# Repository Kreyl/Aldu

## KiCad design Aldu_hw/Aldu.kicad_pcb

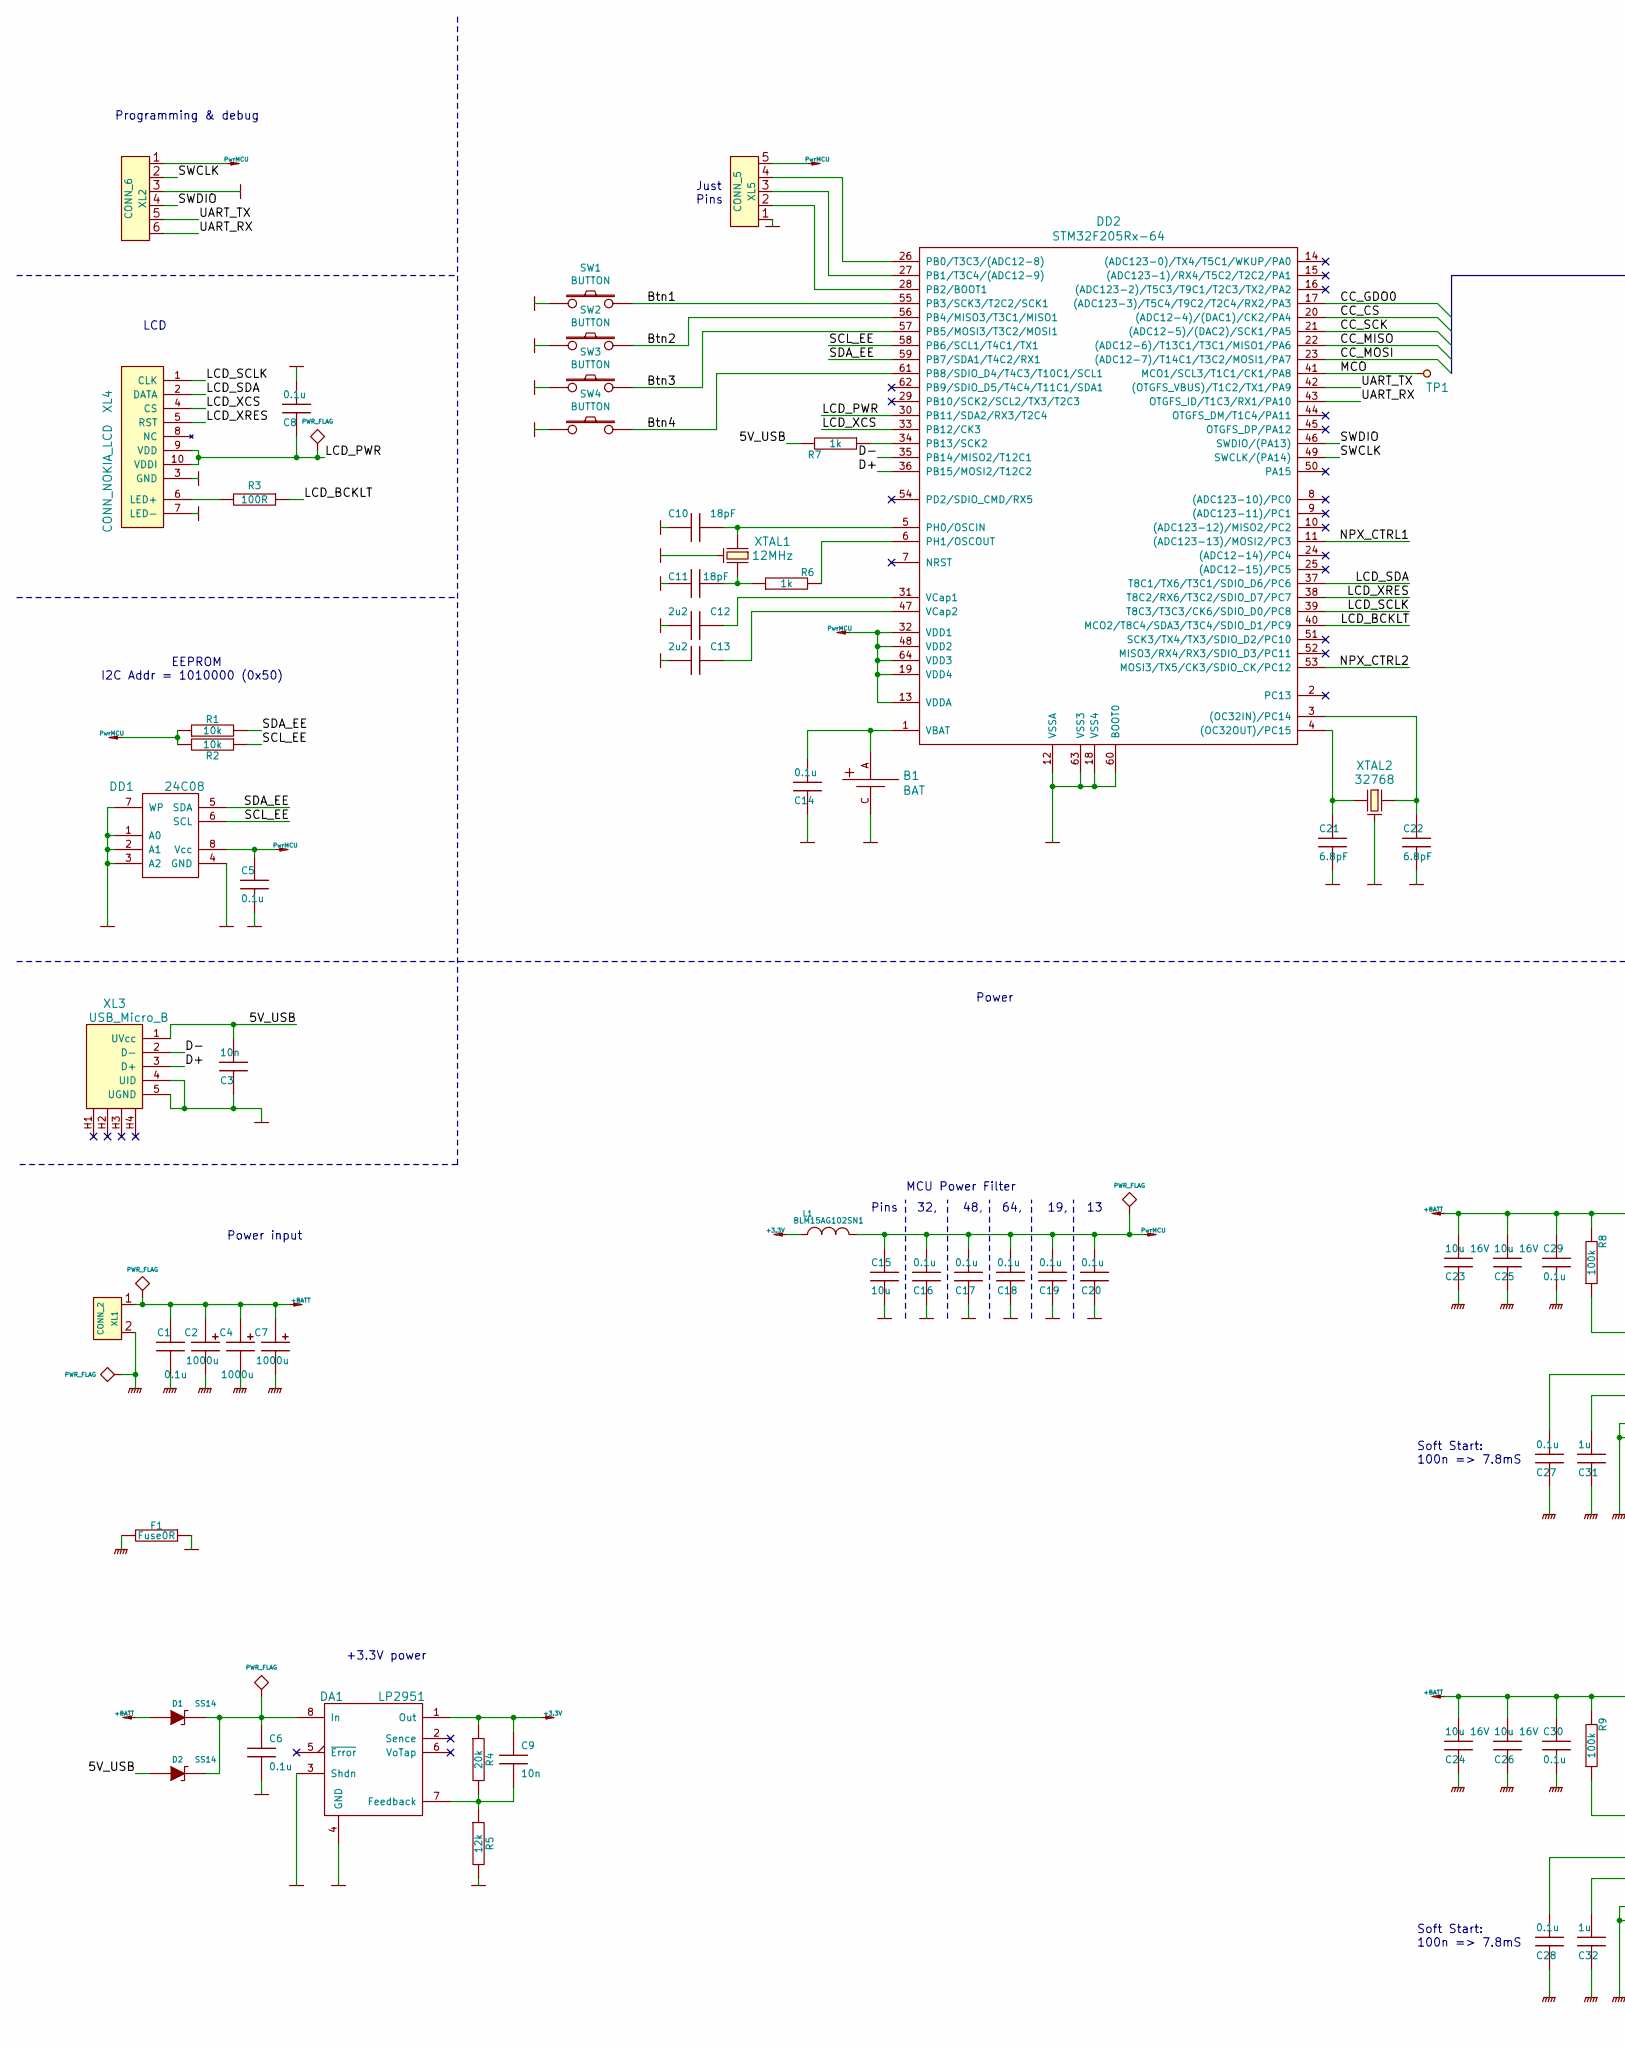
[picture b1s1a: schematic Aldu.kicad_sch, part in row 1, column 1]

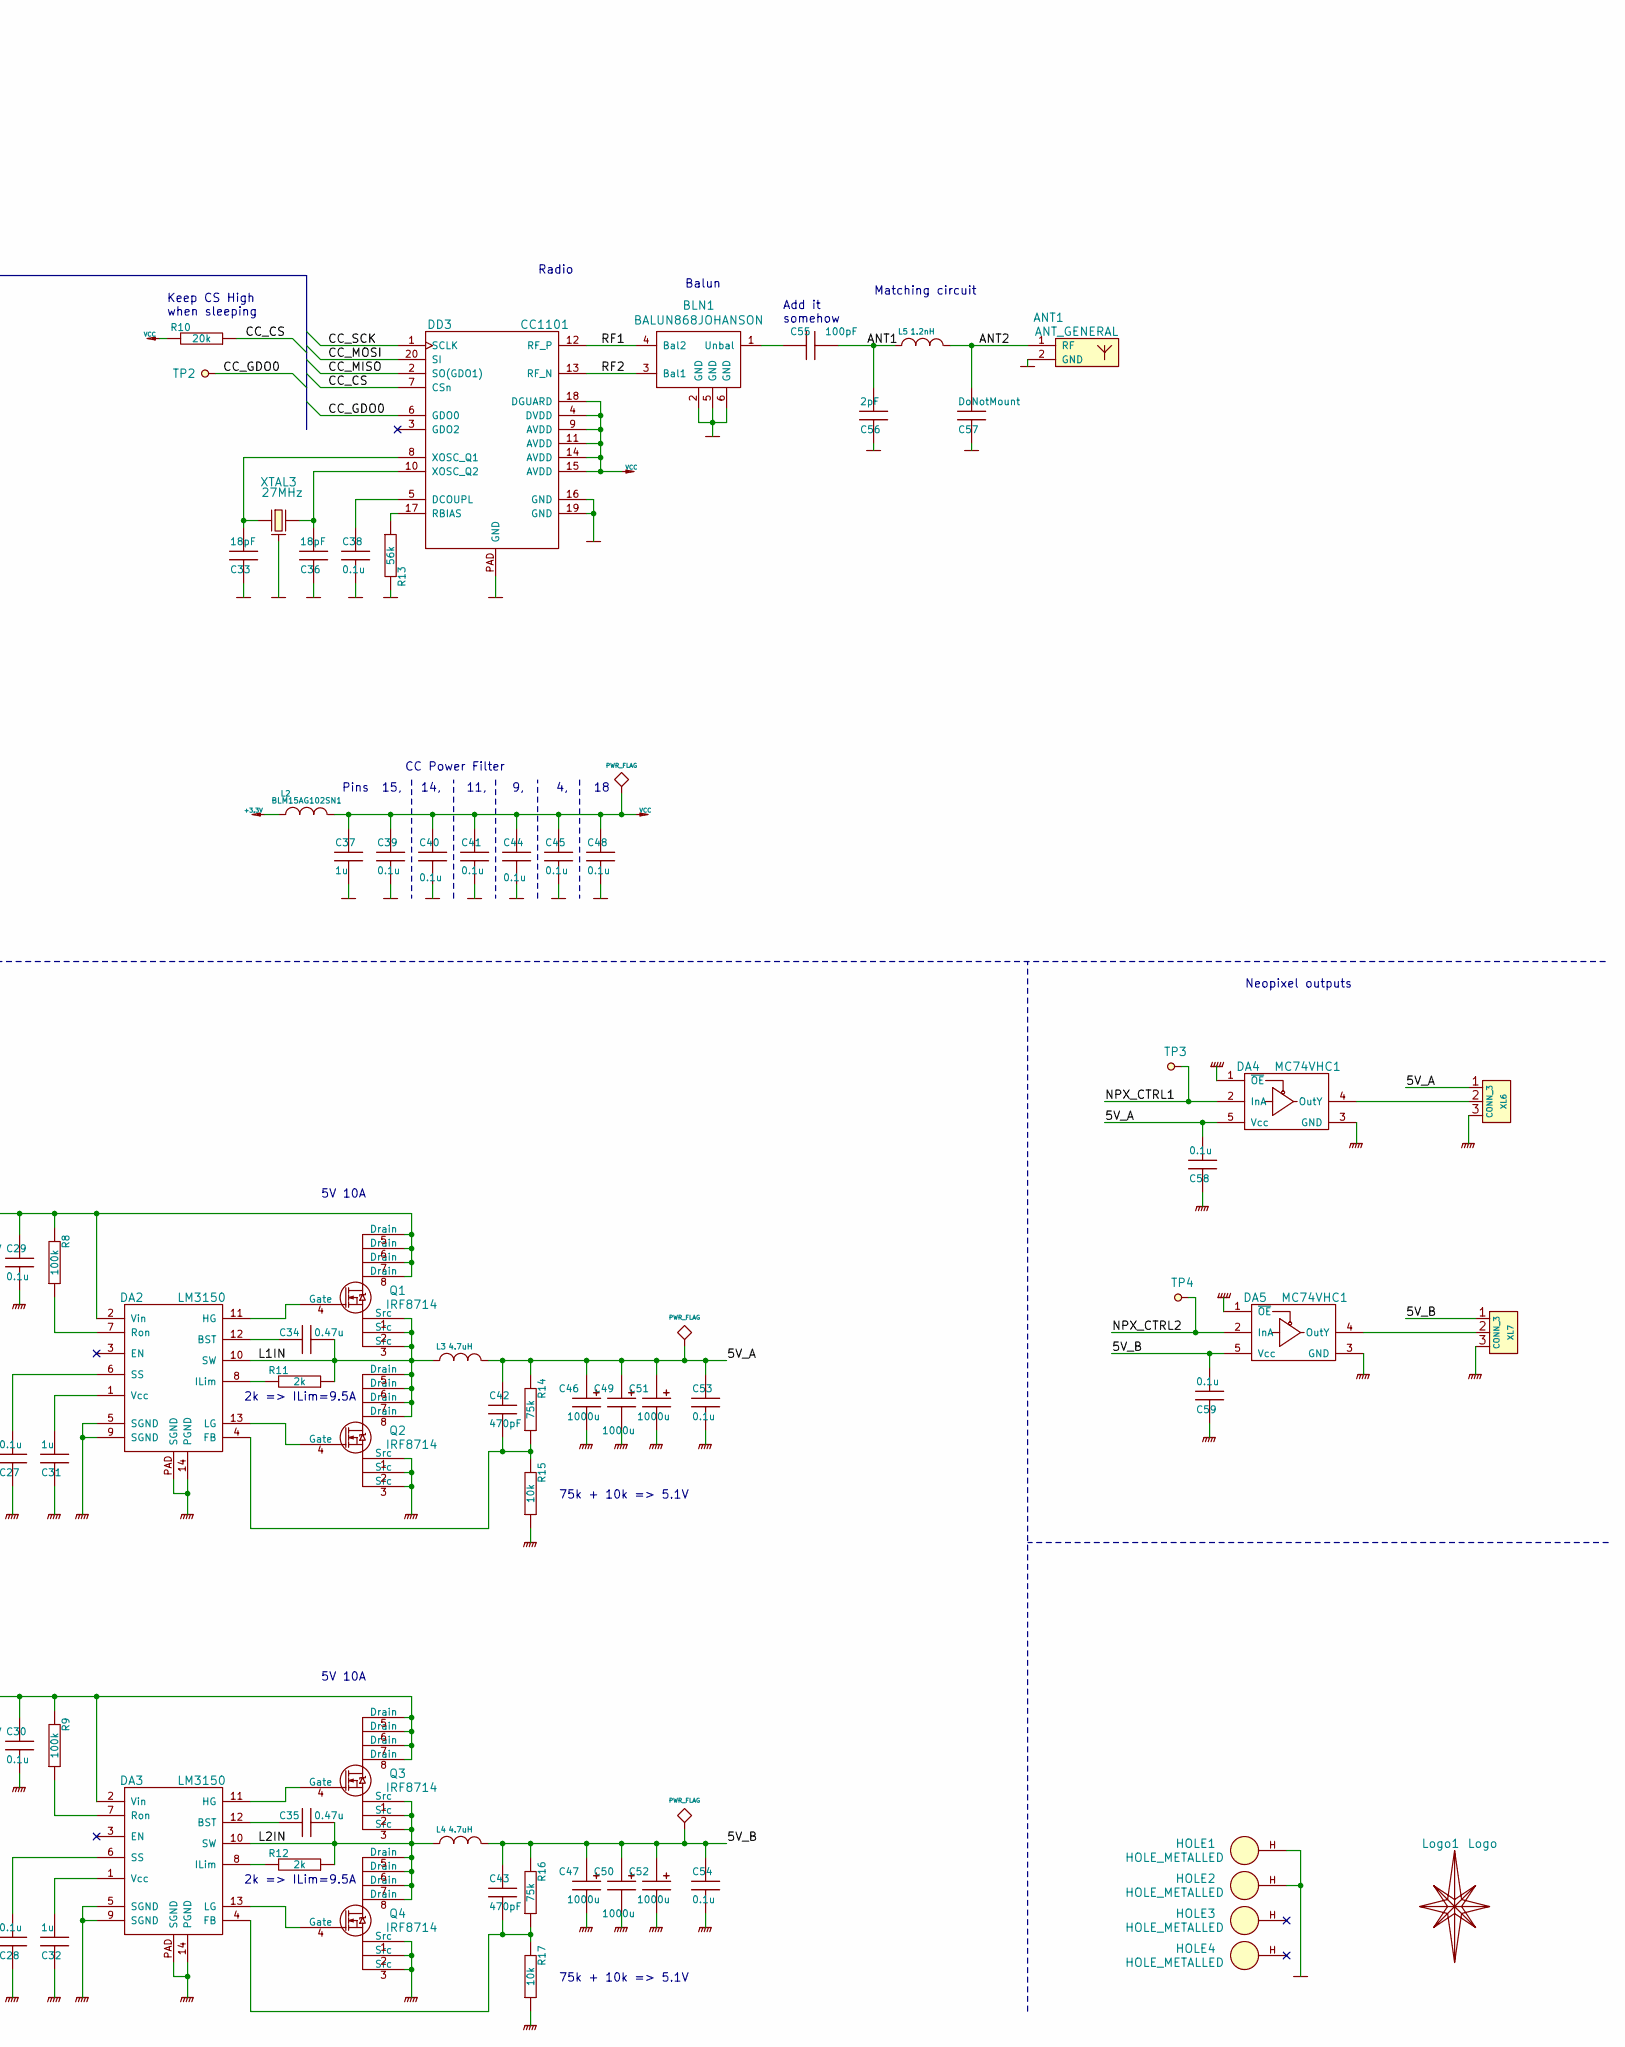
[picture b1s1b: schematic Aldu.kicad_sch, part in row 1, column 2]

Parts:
ANT1: ANT_GENERAL; ANT_868_IFA_SIMPLEJOY
B1: BAT; BATTERY_CH7410
BLN1: BALUN868JOHANSON; BALUN_JOHANSON868
C1, C5, C6, C8, C14, C16, C17, C18, C19, C20, C27, C28, C29, C30, C38, C39, C40, C41, C44, C45, C48, C53, C54, C58, C59: 0.1u; CAP_0603
C2, C4, C7, C46, C47, C49, C50, C51, C52: 1000u; CAP_10xxR
C3, C9: 10n; CAP_0603
C10, C11, C33, C36: 18pF; CAP_0603
C12, C13: 2u2; CAP_0603
C15: 10u; CAP_0603
C21, C22: 6.8pF; CAP_0603
C23, C24, C25, C26: 10u 16V; CAP_0805
C31, C32, C37: 1u; CAP_0603
C34, C35: 0.47u; CAP_0603
C42, C43: 470pF; CAP_0603
C55: 100pF; CAP_0402
C56: 2pF; CAP_0402
C57: DoNotMount; CAP_0402
D1, D2: SS14; SMA_DO214AC
DA1: LP2951; SO8_150MIL
DA2, DA3: LM3150; HTSSOP14
DA4, DA5: MC74VHC1; SOT23-5
DD1: 24C08; SO8_150MIL
DD2: STM32F205Rx-64; LQFP64
DD3: CC1101; QFN20
F1: Fuse0R; FuseShorted
HOLE1, HOLE2, HOLE3, HOLE4: HOLE_METALLED; Hole3_5_out6mm
L1, L2: BLM15AG102SN1; IND_0402
L3, L4: 4.7uH; 13x13
L5: 1.2nH; IND_0402
Logo1: Logo; Ostranna_12d7_10d1
Q1, Q2, Q3, Q4: IRF8714; SO8_150MIL
R1, R2, R15, R17: 10k; RES_0603
R3: 100R; RES_0603
R4, R10: 20k; RES_0603
R5: 12k; RES_0603
R6, R7: 1k; RES_0603
R8, R9: 100k; RES_0603
R11, R12: 2k; RES_0603
R13: 56k; RES_0603
R14, R16: 75k; RES_0603
SW1, SW2, SW3, SW4: BUTTON; BTN_6x6_4x4
TP1, TP2, TP3, TP4: TESTPOINT; TESTPOINT_1MM
XL1: CONN_2; TermiBlockHeader_508_x2_R
XL2: CONN_6; PLS-6
XL3: USB_Micro_B; USBmicro_MOLEX_WM17142
XL4: CONN_NOKIA_LCD; NOKIA_10PIN
XL5: CONN_5; PLS-5
XL6, XL7: CONN_3; TermiBlockHeader_508_x3_R
XTAL1: 12MHz; 0503x4-4
XTAL2: 32768; KX26
XTAL3: 27MHz; 03225C4

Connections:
+3.3V: C9.1, DA1.1 (Out), L1.2, L2.2, R4.1
+BATT: C1.2, C2.1, C4.1, C7.1, C23.1, C24.1, C25.1, C26.1, C29.2, C30.2, D1.A, DA2.2 (Vin), DA3.2 (Vin), Q1.5 (Drain), Q1.6 (Drain), Q1.7 (Drain), Q1.8 (Drain), Q3.5 (Drain), Q3.6 (Drain), Q3.7 (Drain), Q3.8 (Drain), R8.2, R9.2, XL1.1
/5V_A: C42.2, C46.1, C49.1, C51.1, C53.2, C58.1, DA4.5 (Vcc), L3.1, R14.2, XL6.1
/5V_B: C43.2, C47.1, C50.1, C52.1, C54.2, C59.1, DA5.5 (Vcc), L4.1, R16.2, XL7.1
/5V_USB: C3.1, D2.A, R7.2, XL3.1 (UVcc)
/ANT1: C55.1, C56.1, L5.2
/ANT2: ANT1.1 (RF), C57.1, L5.1
/Btn1: DD2.55 (PB3/SCK3/T2C2/SCK1), SW1.2
/Btn2: DD2.56 (PB4/MISO3/T3C1/MISO1), SW2.2
/Btn3: DD2.57 (PB5/MOSI3/T3C2/MOSI1), SW3.2
/Btn4: DD2.61 (PB8/SDIO_D4/T4C3/T10C1/SCL1), SW4.2
/CC_CS: DD2.20 ((ADC12-4)/(DAC1)/CK2/PA4), DD3.7 (CSn), R10.1
/CC_GDO0: DD2.17 ((ADC123-3)/T5C4/T9C2/T2C4/RX2/PA3), DD3.6 (GDO0), TP2.1
/CC_MISO: DD2.22 ((ADC12-6)/T13C1/T3C1/MISO1/PA6), DD3.2 (SO(GDO1))
/CC_MOSI: DD2.23 ((ADC12-7)/T14C1/T3C2/MOSI1/PA7), DD3.20 (SI)
/CC_SCK: DD2.21 ((ADC12-5)/(DAC2)/SCK1/PA5), DD3.1 (SCLK)
/D+: DD2.36 (PB15/MOSI2/T12C2), XL3.3 (D+)
/D-: DD2.35 (PB14/MISO2/T12C1), XL3.2 (D-)
/L1IN: C34.1, DA2.10 (SW), L3.2, Q1.1 (Src), Q1.2 (Src), Q1.3 (Src), Q2.5 (Drain), Q2.6 (Drain), Q2.7 (Drain), Q2.8 (Drain), R11.1
/L2IN: C35.1, DA3.10 (SW), L4.2, Q3.1 (Src), Q3.2 (Src), Q3.3 (Src), Q4.5 (Drain), Q4.6 (Drain), Q4.7 (Drain), Q4.8 (Drain), R12.1
/LCD_BCKLT: DD2.40 (MCO2/T8C4/SDA3/T3C4/SDIO_D1/PC9), R3.1
/LCD_PWR: C8.1, DD2.30 (PB11/SDA2/RX3/T2C4), XL4.9 (VDD), XL4.10 (VDDI)
/LCD_SCLK: DD2.39 (T8C3/T3C3/CK6/SDIO_D0/PC8), XL4.1 (CLK)
/LCD_SDA: DD2.37 (T8C1/TX6/T3C1/SDIO_D6/PC6), XL4.2 (DATA)
/LCD_XCS: DD2.33 (PB12/CK3), XL4.4 (CS)
/LCD_XRES: DD2.38 (T8C2/RX6/T3C2/SDIO_D7/PC7), XL4.5 (RST)
/MCO: DD2.41 (MCO1/SCL3/T1C1/CK1/PA8), TP1.1
/NPX_CTRL1: DA4.2 (InA), DD2.11 ((ADC123-13)/MOSI2/PC3), TP3.1
/NPX_CTRL2: DA5.2 (InA), DD2.53 (MOSI3/TX5/CK3/SDIO_CK/PC12), TP4.1
/RF1: BLN1.4 (Bal2), DD3.12 (RF_P)
/RF2: BLN1.3 (Bal1), DD3.13 (RF_N)
/SCL_EE: DD1.6 (SCL), DD2.58 (PB6/SCL1/T4C1/TX1), R2.1
/SDA_EE: DD1.5 (SDA), DD2.59 (PB7/SDA1/T4C2/RX1), R1.2
/SWCLK: DD2.49 (SWCLK/(PA14)), XL2.2
/SWDIO: DD2.46 (SWDIO/(PA13)), XL2.4
/UART_RX: DD2.43 (OTGFS_ID/T1C3/RX1/PA10), XL2.6
/UART_TX: DD2.42 ((OTGFS_VBUS)/T1C2/TX1/PA9), XL2.5
GND: ANT1.2 (GND), B1.C, BLN1.2 (GND), BLN1.5 (GND), BLN1.6 (GND), C3.2, C5.1, C6.2, C8.2, C10.2, C11.2, C12.2, C13.2, C14.1, C15.1, C16.2, C17.2, C18.2, C19.2, C20.2, C21.2, C22.2, C33.2, C36.2, C37.2, C38.1, C39.2, C40.2, C41.2, C44.2, C45.2, C48.2, C56.2, C57.2, DA1.3 (Shdn), DA1.4 (GND), DD1.1 (A0), DD1.2 (A1), DD1.3 (A2), DD1.4 (GND), DD1.7 (WP), DD2.12 (VSSA), DD2.18 (VSS4), DD2.60 (BOOT0), DD2.63 (VSS3), DD3.16 (GND), DD3.19 (GND), DD3.PAD (GND), F1.1, HOLE1.H, HOLE2.H, R5.2, R13.2, SW1.1, SW2.1, SW3.1, SW4.1, XL2.3, XL3.4 (UID), XL3.5 (UGND), XL4.3 (GND), XL4.7 (LED-), XL5.1, XTAL1.H, XTAL2.H, XTAL3.H
GNDPWR: C1.1, C2.2, C4.2, C7.2, C23.2, C24.2, C25.2, C26.2, C27.2, C28.2, C29.1, C30.1, C31.2, C32.2, C46.2, C47.2, C49.2, C50.2, C51.2, C52.2, C53.1, C54.1, C58.2, C59.2, DA2.5 (SGND), DA2.9 (SGND), DA2.14 (PGND), DA2.PAD (SGND), DA3.5 (SGND), DA3.9 (SGND), DA3.14 (PGND), DA3.PAD (SGND), DA4.1 (~OE), DA4.3 (GND), DA5.1 (~OE), DA5.3 (GND), F1.2, Q2.1 (Src), Q2.2 (Src), Q2.3 (Src), Q4.1 (Src), Q4.2 (Src), Q4.3 (Src), R15.1, R17.1, XL1.2 (PM), XL6.3, XL7.3
unnamed: B1.A, C14.2, DD2.1 (VBAT)
unnamed: BLN1.1 (Unbal), C55.2
unnamed: C6.1, D1.C, D2.C, DA1.8 (In)
unnamed: C9.2, DA1.7 (Feedback), R4.2, R5.1
unnamed: C10.1, DD2.5 (PH0/OSCIN), XTAL1.1
unnamed: C11.1, R6.1, XTAL1.2
unnamed: C12.1, DD2.31 (VCap1)
unnamed: C13.1, DD2.47 (VCap2)
unnamed: C21.1, DD2.4 ((OC32OUT)/PC15), XTAL2.2
unnamed: C22.1, DD2.3 ((OC32IN)/PC14), XTAL2.1
unnamed: C27.1, DA2.6 (SS)
unnamed: C28.1, DA3.6 (SS)
unnamed: C31.1, DA2.1 (Vcc)
unnamed: C32.1, DA3.1 (Vcc)
unnamed: C33.1, DD3.8 (XOSC_Q1), XTAL3.1
unnamed: C34.2, DA2.12 (BST)
unnamed: C35.2, DA3.12 (BST)
unnamed: C36.1, DD3.10 (XOSC_Q2), XTAL3.2
unnamed: C38.2, DD3.5 (DCOUPL)
unnamed: C42.1, DA2.4 (FB), R14.1, R15.2
unnamed: C43.1, DA3.4 (FB), R16.1, R17.2
unnamed: DA2.7 (Ron), R8.1
unnamed: DA2.8 (ILim), R11.2
unnamed: DA2.11 (HG), Q1.4 (Gate)
unnamed: DA2.13 (LG), Q2.4 (Gate)
unnamed: DA3.7 (Ron), R9.1
unnamed: DA3.8 (ILim), R12.2
unnamed: DA3.11 (HG), Q3.4 (Gate)
unnamed: DA3.13 (LG), Q4.4 (Gate)
unnamed: DA4.4 (OutY), XL6.2 (PM)
unnamed: DA5.4 (OutY), XL7.2 (PM)
unnamed: DD2.6 (PH1/OSCOUT), R6.2
unnamed: DD2.26 (PB0/T3C3/(ADC12-8)), XL5.4
unnamed: DD2.27 (PB1/T3C4/(ADC12-9)), XL5.3
unnamed: DD2.28 (PB2/BOOT1), XL5.2
unnamed: DD2.34 (PB13/SCK2), R7.1
unnamed: DD3.17 (RBIAS), R13.1
unnamed: R3.2, XL4.6 (LED+)
PwrMCU: C5.2, C15.2, C16.1, C17.1, C18.1, C19.1, C20.1, DD1.8 (Vcc), DD2.13 (VDDA), DD2.19 (VDD4), DD2.32 (VDD1), DD2.48 (VDD2), DD2.64 (VDD3), L1.1, R1.1, R2.2, XL2.1, XL5.5
VCC: C37.1, C39.1, C40.1, C41.1, C44.1, C45.1, C48.1, DD3.4 (DVDD), DD3.9 (AVDD), DD3.11 (AVDD), DD3.14 (AVDD), DD3.15 (AVDD), DD3.18 (DGUARD), L2.1, R10.2

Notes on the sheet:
EEPROM I2C Addr = 1010000 (0x50)
Programming & debug
LCD
Power input
+3.3V power
Just Pins
Pins 32, 48, 64, 19, 13
MCU Power Filter
Power
Soft Start: 100n => 7.8mS
Keep CS High when sleeping
2k => ILim=9.5A
5V 10A
Pins 15, 14, 11, 9, 4, 18
CC Power Filter
Radio
75k + 10k => 5.1V
Balun
Add it somehow
Matching circuit
Neopixel outputs

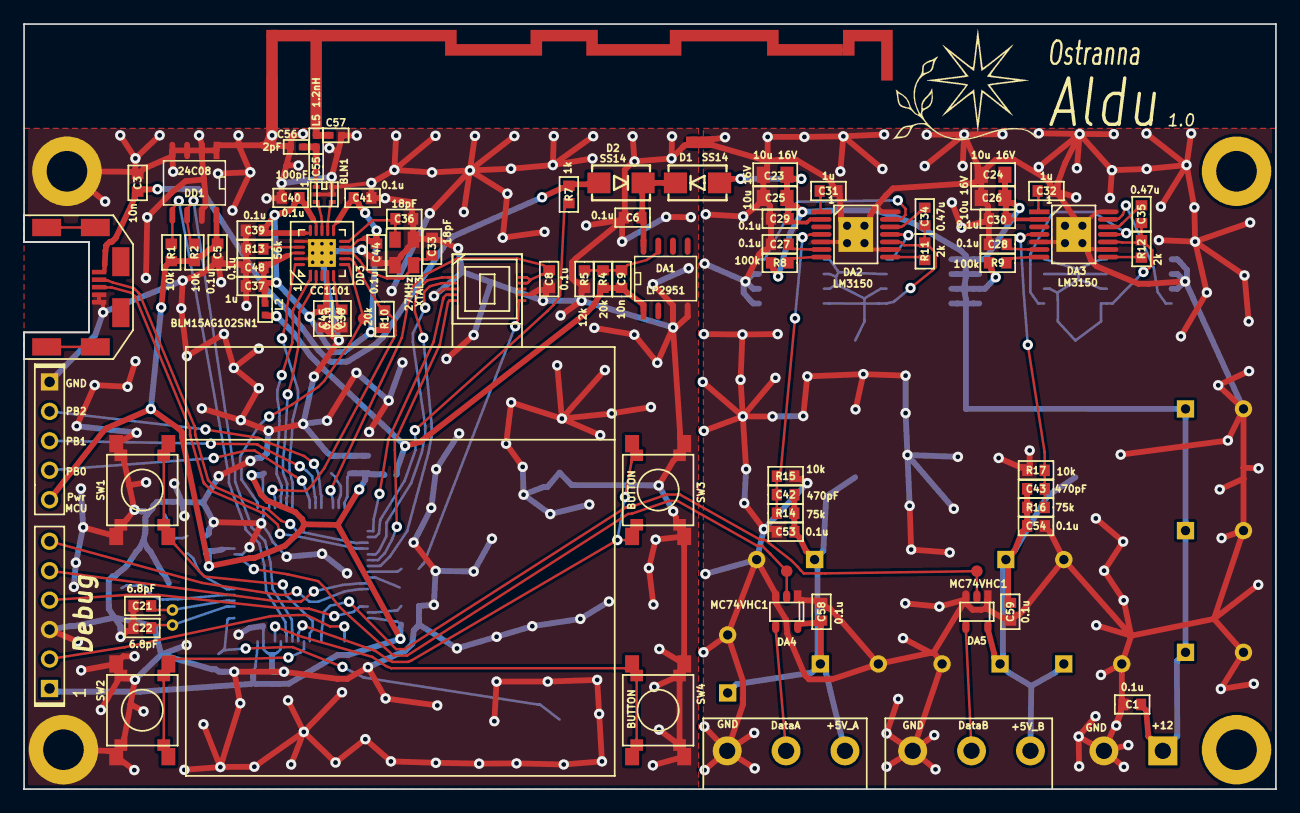
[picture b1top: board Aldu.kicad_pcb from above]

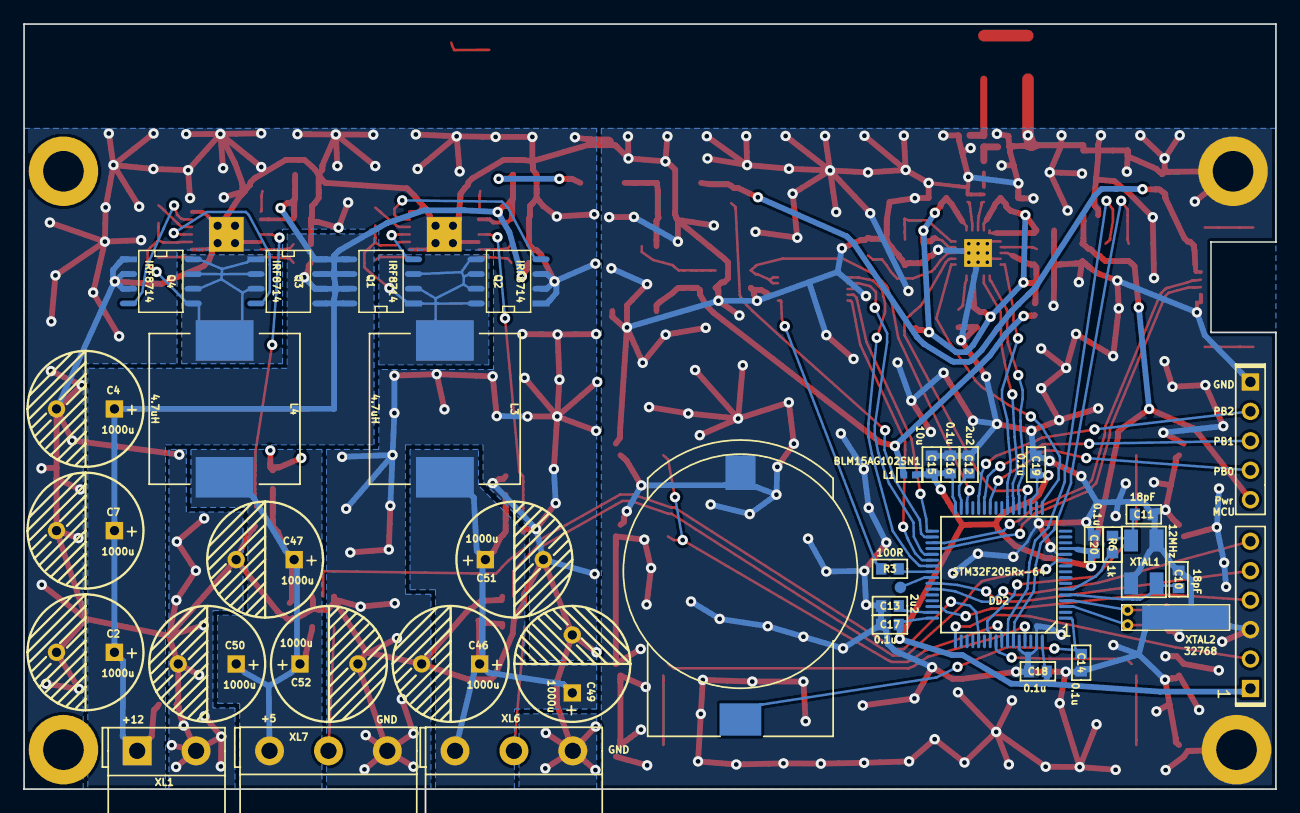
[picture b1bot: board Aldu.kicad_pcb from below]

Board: 2 copper layers, 108.0 x 66.0 mm, 122 parts (37 on the bottom side), 79 nets.

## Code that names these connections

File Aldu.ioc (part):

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Mcu.Name=STM32F205R(B-C-E-F-G)Tx
Mcu.Package=LQFP64
Mcu.UserName=STM32F205RBTx
PA10.Mode=Asynchronous
PA10.Signal=USART1_RX
PA13.Mode=Serial_Wire
PA13.Signal=SYS_JTMS-SWDIO
PA14.Mode=Serial_Wire
PA14.Signal=SYS_JTCK-SWCLK
PA3.Signal=GPIO_Input
PA4.Signal=GPIO_Output
PA5.Mode=Full_Duplex_Master
PA5.Signal=SPI1_SCK
PA6.Mode=Full_Duplex_Master
PA6.Signal=SPI1_MISO
PA7.Mode=Full_Duplex_Master
PA7.Signal=SPI1_MOSI
PA8.Mode=Clock-out-1
PA8.Signal=RCC_MCO_1
PA9.Mode=Asynchronous
PA9.Signal=USART1_TX
PB10.Mode=TX_Only_Simplex_Unidirect_Master
PB10.Signal=SPI2_SCK
PB11.Signal=GPIO_Output
PB12.Signal=GPIO_Output
PB13.Mode=Activate_VBUS_FS
PB13.Signal=USB_OTG_HS_VBUS
PB14.Mode=Device_Only_FS
PB14.Signal=USB_OTG_HS_DM
PB15.Mode=Device_Only_FS
PB15.Signal=USB_OTG_HS_DP
PB3.Mode=TX_Only_Simplex_Unidirect_Master
PB3.Signal=SPI3_SCK
PB4.Signal=GPIO_Input
PB5.Signal=GPIO_Input
PB6.Mode=I2C
PB6.Signal=I2C1_SCL
PB7.Mode=I2C
PB7.Signal=I2C1_SDA
PB8.Signal=GPIO_Input
PC12.Mode=TX_Only_Simplex_Unidirect_Master
PC12.Signal=SPI3_MOSI
PC14-OSC32_IN.Mode=LSE-External-Oscillator
PC14-OSC32_IN.Signal=RCC_OSC32_IN
PC15-OSC32_OUT.Mode=LSE-External-Oscillator
PC15-OSC32_OUT.Signal=RCC_OSC32_OUT
PC3.Mode=TX_Only_Simplex_Unidirect_Master
PC3.Signal=SPI2_MOSI
PC6.Mode=Synchronous
PC6.Signal=USART6_TX
PC7.Mode=Synchronous
PC7.Signal=USART6_RX
PC8.Mode=Synchronous
PC8.Signal=USART6_CK
PC9.Signal=S_TIM3_CH4
PH0-OSC_IN.Mode=HSE-External-Oscillator
PH0-OSC_IN.Signal=RCC_OSC_IN
PH1-OSC_OUT.Mode=HSE-External-Oscillator
PH1-OSC_OUT.Signal=RCC_OSC_OUT
RCC.HSE_VALUE=12000000
RCC.SYSCLKFreq_VALUE=32000000
RCC.SYSCLKSource=RCC_SYSCLKSOURCE_PLLCLK

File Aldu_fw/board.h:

/*
 * board.h
 *
 *  Created on: 12 ����. 2015 �.
 *      Author: Kreyl
 */

#pragma once

#include <inttypes.h>

// ==== General ====
#define BOARD_NAME          "Aldu10"
#define APP_NAME            "Arc"

// MCU type as defined in the ST header.
#define STM32F205xx

// Freq of external crystal if any. Leave it here even if not used.
#define CRYSTAL_FREQ_HZ 12000000

// OS timer settings
#define STM32_ST_IRQ_PRIORITY   2
#define STM32_ST_USE_TIMER      5
#define SYS_TIM_CLK             (Clk.GetTimInputFreq(TIM5))

//  Periphery
#define I2C1_ENABLED            FALSE
#define I2C2_ENABLED            FALSE
#define I2C3_ENABLED            FALSE
#define SIMPLESENSORS_ENABLED   FALSE
#define BUTTONS_ENABLED         FALSE

#define ADC_REQUIRED            FALSE


#define LED_CNT                 150L   // Number of LEDs


#if 1 // ========================== GPIO =======================================
// EXTI
#define INDIVIDUAL_EXTI_IRQ_REQUIRED    FALSE

// UART
#define UART_GPIO       GPIOA
#define UART_TX_PIN     9
#define UART_RX_PIN     10

// Buttons
#define BTN1_PIN        GPIOB, 3
#define BTN2_PIN        GPIOB, 4
#define BTN3_PIN        GPIOB, 5
#define BTN4_PIN        GPIOB, 8

// LCD
#define LCD_SDA         GPIOC, 6
#define LCD_XRES        GPIOC, 7
#define LCD_SCLK        GPIOC, 8
#define LCD_AF          AF8
#define LCD_XCS         GPIOB, 12
#define LCD_BCKLT       { GPIOC, 9, TIM3, 4, invNotInverted, omPushPull, 100 }
#define LCD_PWR         GPIOB, 11

// Neopixel
#define NPX_SPI_A       SPI2
#define NPX_GPIO_A      GPIOC
#define NPX_PIN_A       3
#define NPX_AF_A        AF5

#define NPX_SPI_B       SPI3
#define NPX_GPIO_B      GPIOC
#define NPX_PIN_B       12
#define NPX_AF_B        AF6

// I2C
#define I2C1_GPIO       GPIOB
#define I2C1_SCL        6
#define I2C1_SDA        7

// USB
#define USB_DETECT_PIN  GPIOB, 13
#define USB_DM          GPIOB, 14
#define USB_DP          GPIOB, 15
#define USB_AF          AF10

// Radio: SPI, PGpio, Sck, Miso, Mosi, Cs, Gdo0
#define CC_Setup0       SPI1, GPIOA, 5,6,7, GPIOA,4, GPIOA,3

#endif // GPIO



#if I2C2_ENABLED // ====================== I2C ================================
#define I2C2_BAUDRATE   400000
#define I2C_PILL        i2c2
#endif

#if ADC_REQUIRED // ======================= Inner ADC ==========================
#define ADC_MEAS_PERIOD_MS  2007
// Clock divider: clock is generated from the APB2
#define ADC_CLK_DIVIDER		adcDiv4

// ADC channels
#define ADC_CHNL_BATTERY    10

#define ADC_CHANNELS        { ADC_CHNL_BATTERY, ADC_CHNL_VREFINT }
#define ADC_CHANNEL_CNT     2   // Do not use countof(AdcChannels) as preprocessor does not know what is countof => cannot check
#define ADC_SAMPLE_TIME     ast84Cycles
#define ADC_SAMPLE_CNT      8   // How many times to measure every channel

#define ADC_MAX_SEQ_LEN     16  // 1...16; Const, see ref man
#define ADC_SEQ_LEN         (ADC_SAMPLE_CNT * ADC_CHANNEL_CNT)
#if (ADC_SEQ_LEN > ADC_MAX_SEQ_LEN) || (ADC_SEQ_LEN == 0)
#error "Wrong ADC channel count and sample count"
#endif
#endif

#if 1 // =========================== DMA =======================================
#define STM32_DMA_REQUIRED  TRUE
// ==== Uart ====
// Remap is made automatically if required
#define UART_DMA_TX     STM32_DMA2_STREAM7
#define UART_DMA_RX     STM32_DMA2_STREAM2
#define UART_DMA_CHNL   4
#define UART_DMA_TX_MODE(Chnl) \
                            (STM32_DMA_CR_CHSEL(Chnl) | \
                            DMA_PRIORITY_LOW | \
                            STM32_DMA_CR_MSIZE_BYTE | \
                            STM32_DMA_CR_PSIZE_BYTE | \
                            STM32_DMA_CR_MINC |       /* Memory pointer increase */ \
                            STM32_DMA_CR_DIR_M2P |    /* Direction is memory to peripheral */ \
                            STM32_DMA_CR_TCIE         /* Enable Transmission Complete IRQ */)

#define UART_DMA_RX_MODE(Chnl) \
                            (STM32_DMA_CR_CHSEL((Chnl)) | \
                            DMA_PRIORITY_MEDIUM | \
                            STM32_DMA_CR_MSIZE_BYTE | \
                            STM32_DMA_CR_PSIZE_BYTE | \
                            STM32_DMA_CR_MINC |       /* Memory pointer increase */ \
                            STM32_DMA_CR_DIR_P2M |    /* Direction is peripheral to memory */ \
                            STM32_DMA_CR_CIRC         /* Circular buffer enable */)

#define LCD_DMA         STM32_DMA2_STREAM6  // USART6 TX
#define LCD_DMA_CHNL    5

#define NPX_DMA_A       STM32_DMA1_STREAM4
#define NPX_DMA_CHNL_A  0
#define NPX_DMA_B       STM32_DMA1_STREAM5
#define NPX_DMA_CHNL_B  0

#if I2C1_ENABLED // ==== I2C1 ====
#define I2C1_DMA_TX     STM32_DMA1_STREAM6
#define I2C1_DMA_RX     STM32_DMA1_STREAM5
#endif
#if I2C2_ENABLED // ==== I2C2 ====
#define I2C2_DMA_TX     STM32_DMA1_STREAM7
#define I2C2_DMA_RX     STM32_DMA1_STREAM3
#endif

#if ADC_REQUIRED
#define ADC_DMA         STM32_DMA2_STREAM0
#define ADC_DMA_MODE    STM32_DMA_CR_CHSEL(0) |   /* DMA2 Stream0 Channel0 */ \
                        DMA_PRIORITY_LOW | \
                        STM32_DMA_CR_MSIZE_HWORD | \
                        STM32_DMA_CR_PSIZE_HWORD | \
                        STM32_DMA_CR_MINC |       /* Memory pointer increase */ \
                        STM32_DMA_CR_DIR_P2M |    /* Direction is peripheral to memory */ \
                        STM32_DMA_CR_TCIE         /* Enable Transmission Complete IRQ */
#endif // ADC

#endif // DMA

#if 1 // ========================== USART ======================================
#define PRINTF_FLOAT_EN FALSE
#define UART_TXBUF_SZ   2048
#define UART_RXBUF_SZ   99
#define CMD_UART_PARAMS \
    USART1, UART_GPIO, UART_TX_PIN, UART_GPIO, UART_RX_PIN, \
    UART_DMA_TX, UART_DMA_RX, UART_DMA_TX_MODE(UART_DMA_CHNL), UART_DMA_RX_MODE(UART_DMA_CHNL)

// LCD USART
#define LCD_UART        USART6
#define LCD_UART_SPEED  100000
#define LCD_UART_EN()   rccEnableUSART6(FALSE)

#endif

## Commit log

2018-06-03 + PCB sent to factory
2018-06-22 First successful compilation
2018-06-22 LCD works
2018-06-22 + Clock works + Buttons
2018-06-22 Time and date setup ok
2018-06-22 + Effects rewritten again
2018-06-22 + SK6812 works ok + Effect AllTogetherSmoothly works ok
2018-06-26 + Release cfg
2021-06-26 Swtch to CubeIDE
2021-06-26 + Radio works + LEDs timings seem good
2021-06-27 Seems working
2021-07-03 + RC
